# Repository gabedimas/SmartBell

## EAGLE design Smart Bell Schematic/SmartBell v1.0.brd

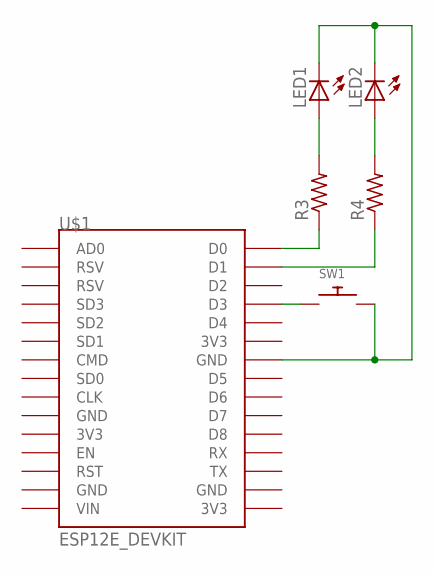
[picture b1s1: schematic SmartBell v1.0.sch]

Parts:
LED1, LED2: LED5MM
R3, R4: R-US_0207/10; 0207/10
SW1: SWITCH_PUSHBUTTONSOFTTOUCHSMD_SJ; PUSHBUTTON_SMD_SJ
U$1: ESP12E_DEVKIT

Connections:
unnamed: LED1.A, R3.2
unnamed: LED2.A, R4.2
unnamed: R3.1, U$1.D0
unnamed: R4.1, U$1.D1
unnamed: LED1.K (C), LED2.K (C), SW1.P$2, U$1.GND@2 (GND)
unnamed: SW1.P$1, U$1.D3

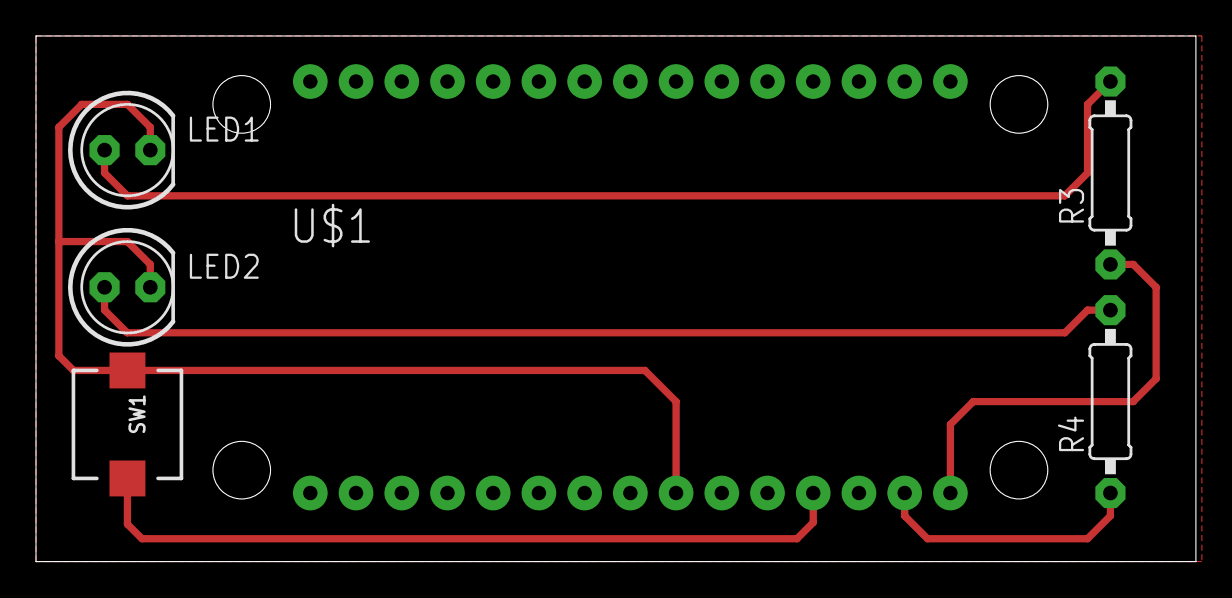
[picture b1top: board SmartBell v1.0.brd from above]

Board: 2 copper layers, 64.4 x 29.2 mm, 6 parts (0 on the bottom side), 6 nets.
